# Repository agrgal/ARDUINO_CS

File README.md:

# ARDUINO_CS

Esta carpeta archivará los trabajos que he realizado de Arduino en los últimos años. Servirá de contenedor y ejemplo de los mismos

### Arduino_mis_proyectos

Encontrarás aquí una serie de proyectos de Arduino. Son mis trabajos a lo largo de unos diez años. 

1. [Cubo de leds](https://github.com/agrgal/ARDUINO_CS/tree/master/ARDUINO_mis_proyectos/4ESO_2016_POV_Cubo_LEDS)

2. [Luces de freno e intermitentes para una bicicleta](https://github.com/agrgal/ARDUINO_CS/tree/master/ARDUINO_mis_proyectos/BICICLETA)

3. [Experimentos de Física con Arduino](https://github.com/agrgal/ARDUINO_CS/tree/master/ARDUINO_mis_proyectos/EXPERIMENTOS%20FISICA_QUIMICA). Relacionado con éste último mi ponencia en Málaga [Ponencia](https://github.com/agrgal/ARDUINO_CS/tree/master/ARDUINO_mis_proyectos/PONENCIA_MALAGA)

4. [Estación meteorológica] (https://github.com/agrgal/ARDUINO_CS/tree/master/ARDUINO_mis_proyectos/Estacion_meteorologica)

5. [Luces para una escalera](https://github.com/agrgal/ARDUINO_CS/tree/master/ARDUINO_mis_proyectos/Luz%20de%20escalera)

6. Último añadido. [Proyecto de mando infrarrojo para proyectores](https://github.com/agrgal/ARDUINO_CS/tree/master/ARDUINO_mis_proyectos/proyecto_infrarrojo) relacionado con [Mando proyector](https://github.com/agrgal/ARDUINO_CS/tree/master/ARDUINO_mis_proyectos/MANDO%20Proyector)

7. [Proyecto Boom](https://github.com/agrgal/ARDUINO_CS/tree/master/ARDUINO_mis_proyectos/Proyecto_boom). Juego presentado en la feria de la Ciencia de Jerez emulando el juego de televisión en el que hay que eliminar respuestas incorrectas a una pregunta. Quizás uno de los proyectos de los que me siento más satisfecho, tanto del trabajo del alumnado como del mío. [Instrucciones ](https://github.com/agrgal/ARDUINO_CS/blob/master/ARDUINO_mis_proyectos/Proyecto_boom/Proyecto%20Boom.pptx)

8. [Reloj con alarma y cronómetro](https://github.com/agrgal/ARDUINO_CS/tree/master/ARDUINO_mis_proyectos/Reloj_cronometro). Proyecto en el que construí un reloj con un display de 4 dígitos 7 segmentos usando únicamente una placa Arduino, controlando el overflow de la orden millis(). Ampliación a usarlo como cronómetro simplemente cambiando el programa.

9. [Semáforo acústico](https://github.com/agrgal/ARDUINO_CS/tree/master/ARDUINO_mis_proyectos/Sem%C3%A1foro_ac%C3%BAstico)

10. [Sensor de temperatura](https://github.com/agrgal/ARDUINO_CS/tree/master/ARDUINO_mis_proyectos/Sensor_temperatura)

11. [Tutoriales sobre Arduino](https://github.com/agrgal/ARDUINO_CS/tree/master/ARDUINO_mis_proyectos/TUTORIALES)

12. [Apuntes relacionados con VISUALINO. Programación por bloques](https://github.com/agrgal/ARDUINO_CS/tree/master/ARDUINO_mis_proyectos/VISUALINO). Publicados también en PROCOMÚN. [Enlace 1](http://procomun.educalab.es/es/ode/view/1453974406581) y [Enlace 2](http://procomun.educalab.es/es/ode/view/1453974407097)

### Copia de seguridad de mis sketches de Arduino

[Enlace a la carpeta](https://github.com/agrgal/ARDUINO_CS/tree/master/Carpeta_de_proyectos_Arduino_copia_de_seguridad)

### Carpetas con el curso impartido en IES Fernando Savater sobre Arduino Avanzado: presentaciones y PDFS

Trato aspectos como implementar una alimentación con baterías recargables, grabar datos, programar un ATtiny85, receptor infrarrojo, DFPlayer_Mini, control de motores paso a paso, y un estudio teórico de ciertos aspectos: registros, interrupciones, multitarea, timers, overflow de millis() y programación orientada a objetos.

1. [Presentaciones del curso](https://github.com/agrgal/ARDUINO_CS/tree/master/Curso_Arduino_Savater_Febrero_2020)

2. [Presentaciones del curso en PDF](https://github.com/agrgal/ARDUINO_CS/tree/master/Curso_Arduino_Savater_Febrero_2020_PDFs)

### NodeMCU (ESP8266_ESP32_Proyectos)

Copia de seguridad de los artículos publicados en mi [blog](https://agrportfolioeducativo.blogspot.com/). En él trato temas como Firebase y el protocolo ESPNOW. También está descrito un proyecto inacabado, botón del pánico, manejo de una CNC y grabado de pcbs, algo de diseño con FREECAD,dibujo en pantallas OLED 128x64.

1.Índice de entradas con mis estudios sobre el NodeMCU: [enlace](https://agrportfolioeducativo.blogspot.com/2019/07/indice-de-nodemcu.html)

2.Índice de entradas botón del pánico: [enlace](https://agrportfolioeducativo.blogspot.com/2019/12/listado-de-entradas-boton-del-panico.html)

Es preferible consultar el blog antes de descargar los documentos PDF. En la carpeta de sketches pueden encontrarse la mayoría de los programas usados con el NODEMCU correspondiente a las diferentes entradas.

3.Proyecto IoT. Luces de lectura definitivo. También en el sitio [Luces de Lectura](https://github.com/agrgal/LucesLectura)

### Robótica

Algunos apuntes de robótica con PrintBOT [Robótica](https://github.com/agrgal/ARDUINO_CS/tree/master/ROBOTICA)

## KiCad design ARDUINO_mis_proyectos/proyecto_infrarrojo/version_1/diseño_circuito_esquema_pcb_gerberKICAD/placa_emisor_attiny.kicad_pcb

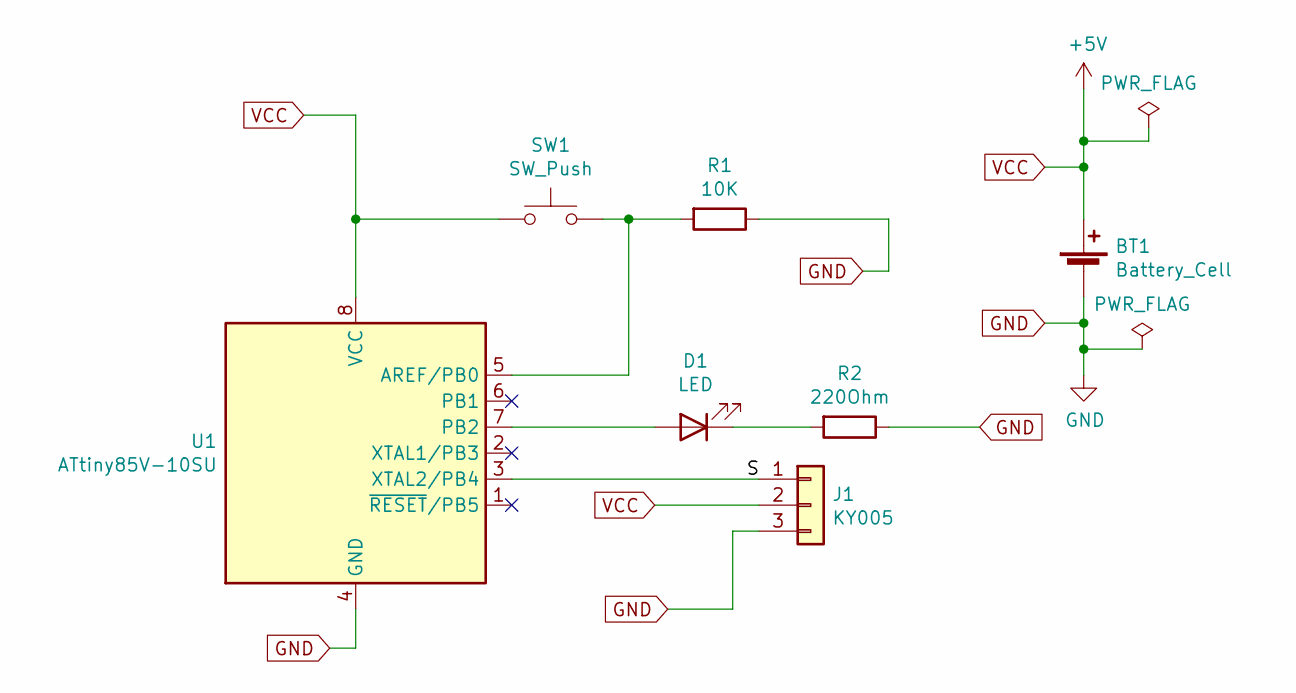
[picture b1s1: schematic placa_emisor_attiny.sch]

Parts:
BT1: Battery_Cell; BatteryHolder_Keystone_106_1x20mm
D1: LED; LED_D5.0mm
J1: KY005; PinHeader_1x03_P2.54mm_Horizontal
R1: 10K; R_Axial_DIN0207_L6.3mm_D2.5mm_P10.16mm_Horizontal
R2: 220Ohm; R_Axial_DIN0207_L6.3mm_D2.5mm_P10.16mm_Horizontal
SW1: SW_Push; SW_PUSH_6mm_H13mm
U1: ATtiny85V-10SU; DIP-8_W7.62mm_Socket_LongPads

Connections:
/S: J1.1, U1.3 (XTAL2/PB4)
GND: BT1.2 (-), J1.3, R1.1, R2.1, U1.4 (GND)
unnamed: D1.1 (K), R2.2
unnamed: D1.2 (A), U1.7 (PB2)
unnamed: R1.2, SW1.2, U1.5 (AREF/PB0)
VCC: BT1.1 (+), J1.2, SW1.1, U1.8 (VCC)

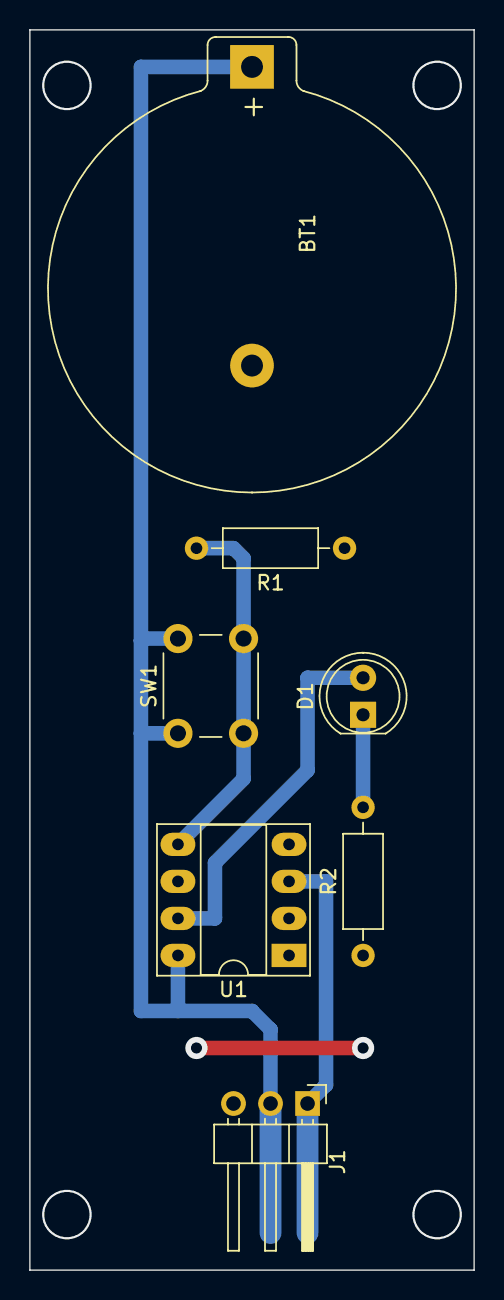
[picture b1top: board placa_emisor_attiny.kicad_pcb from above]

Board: 2 copper layers, 30.5 x 85.1 mm, 7 parts (0 on the bottom side), 6 nets.

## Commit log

2020-02-22 Mi primera subida
2020-02-22 modificaciones a la carpeta Savater
2020-02-22 Copia seguridad mis ficheros arduino
2020-02-23 Todos los proyectos del DRIVE
2020-02-27 borrado del antiguo Savater
2020-02-27 actualización curso del Savater
2020-02-27 subida de los pdfs
2021-01-09 añadiendo el proyecto del mando infrarrojo
2021-01-09 actualización de programas ARDUINO
2021-01-10 Modificando el Readme.md al renovar la información
    Día 10-1-2020. Finalizado el proceso de recuperación del disco duro de mi ordenador y haciendo un clone al mismo, aprovecho para modificar el readme.
2021-01-10 añadiendo copia de apuntes NodeMCU del blog
2021-01-10 Actualización tras publicar los documentos NodeMCU
    Una vez descargadas y publicadas las entradas correspondientes al NodeMCU, actualizo el readme
2021-01-10 Actualización Readme
    Añado algunos datos más al ReadMe
2021-01-10 Añadiendo programas para usar la pantalla OLED 128x64
2021-01-15 códigos mandos sala informática y otros
2021-01-21 renombrado de carpetas NODEMCU
2021-02-06 añadiendo diseño camiseta
2022-08-29 Actualizando attiny IR Remote
    Algunos cambios en los programas del attiny
2024-02-04 Reunifico github
    Luces de lectura y carpeta con proyectos ESP8266 y ESP32
2024-02-04 Reestructuracion_contenido
    Reestructuración del contenido
2024-02-04 Nueva reestructuración
    Nueva reestructuración
2024-02-04 Copia seguridad Arduino Feb 2024
    Copia seguridad Arduino Feb 2024
2024-02-04 Cambios en el README
    Cambios en el README
